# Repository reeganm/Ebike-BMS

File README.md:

# Ebike-BMS
Battery Management system for an Ebike

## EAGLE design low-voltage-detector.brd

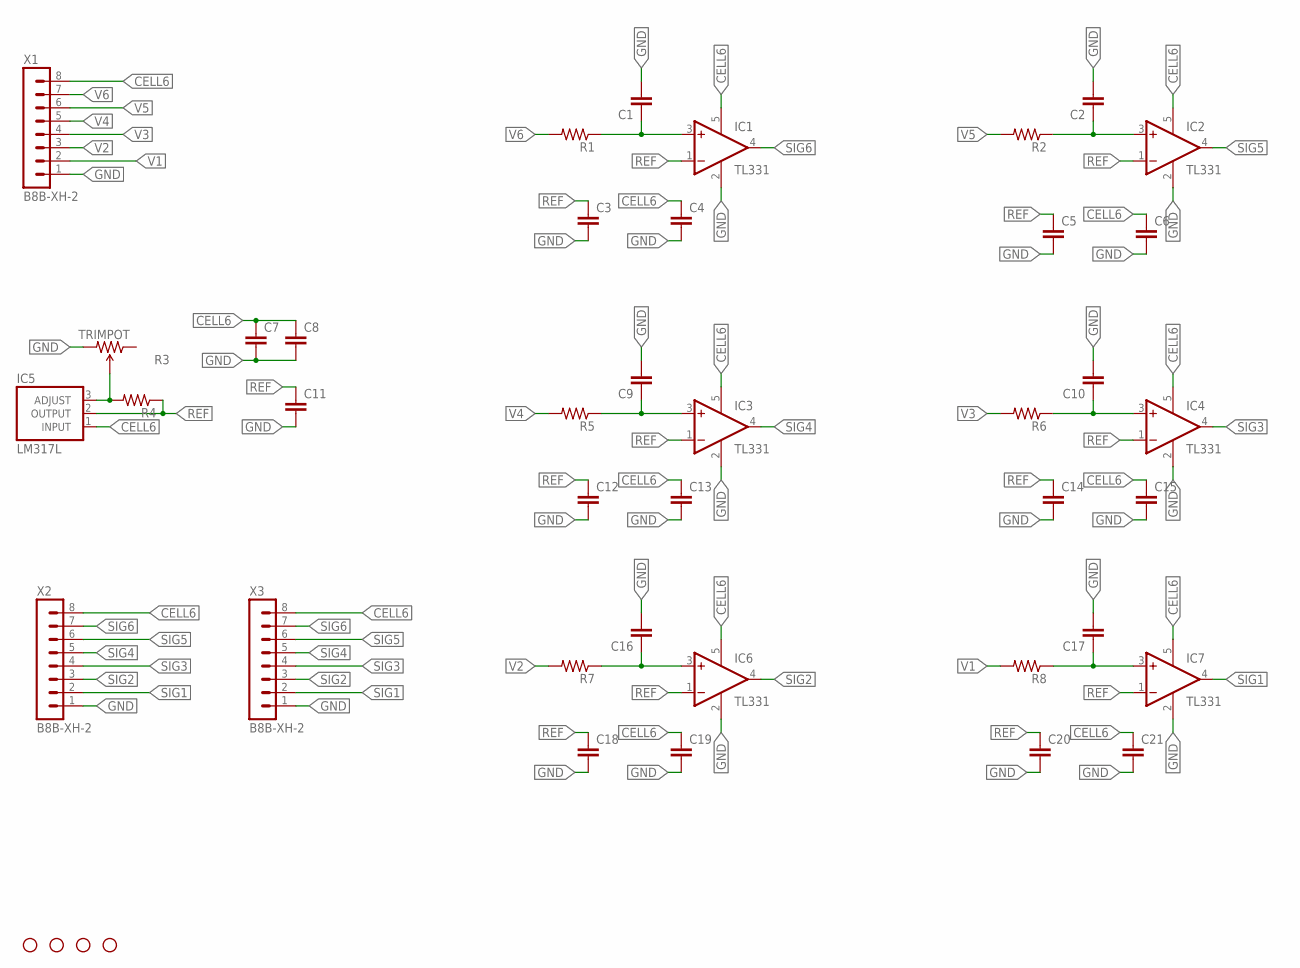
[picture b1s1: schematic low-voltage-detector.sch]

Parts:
C1, C2, C3, C4, C5, C6, C7, C8, C9, C10, C11, C12, C13, C14, C15, C16, C17, C18, C19, C20, C21: CAPACITOR_0805; 0805
H1, H2, H3, H4: STAND-OFF
IC1, IC2, IC3, IC4, IC6, IC7: TL331; DBV-R-PDSO-G5
IC5: LM317L; TO92
R1, R2, R4, R5, R6, R7, R8: R-US_R0805; R0805
R3: TRIMPOT; 490-2877-ND
X1, X2, X3: B8B-XH-2; B8B-XH-A

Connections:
CELL6: C4.1, C6.1, C7.1, C8.1, C13.1, C15.1, C19.1, C21.1, IC1.5 (V+), IC2.5 (V+), IC3.5 (V+), IC4.5 (V+), IC5.1 (INPUT), IC6.5 (V+), IC7.5 (V+), X1.8, X2.8, X3.8
GND: C1.2, C2.2, C3.2, C4.2, C5.2, C6.2, C7.2, C8.2, C9.2, C10.2, C11.2, C12.2, C13.2, C14.2, C15.2, C16.2, C17.2, C18.2, C19.2, C20.2, C21.2, IC1.2 (GND), IC2.2 (GND), IC3.2 (GND), IC4.2 (GND), IC6.2 (GND), IC7.2 (GND), R3.P$3 (CW), X1.1, X2.1, X3.1
unnamed: C1.1, IC1.3 (+IN), R1.1
unnamed: C2.1, IC2.3 (+IN), R2.1
unnamed: C9.1, IC3.3 (+IN), R5.1
unnamed: C10.1, IC4.3 (+IN), R6.1
unnamed: C16.1, IC6.3 (+IN), R7.1
unnamed: C17.1, IC7.3 (+IN), R8.1
unnamed: IC5.3 (ADJUST), R3.P$2 (WIPER), R4.2
REF: C3.1, C5.1, C11.1, C12.1, C14.1, C18.1, C20.1, IC1.1 (-IN), IC2.1 (-IN), IC3.1 (-IN), IC4.1 (-IN), IC5.2 (OUTPUT), IC6.1 (-IN), IC7.1 (-IN), R4.1
SIG1: IC7.4 (OUT), X2.2, X3.2
SIG2: IC6.4 (OUT), X2.3, X3.3
SIG3: IC4.4 (OUT), X2.4, X3.4
SIG4: IC3.4 (OUT), X2.5, X3.5
SIG5: IC2.4 (OUT), X2.6, X3.6
SIG6: IC1.4 (OUT), X2.7, X3.7
V1: R8.2, X1.2
V2: R7.2, X1.3
V3: R6.2, X1.4
V4: R5.2, X1.5
V5: R2.2, X1.6
V6: R1.2, X1.7

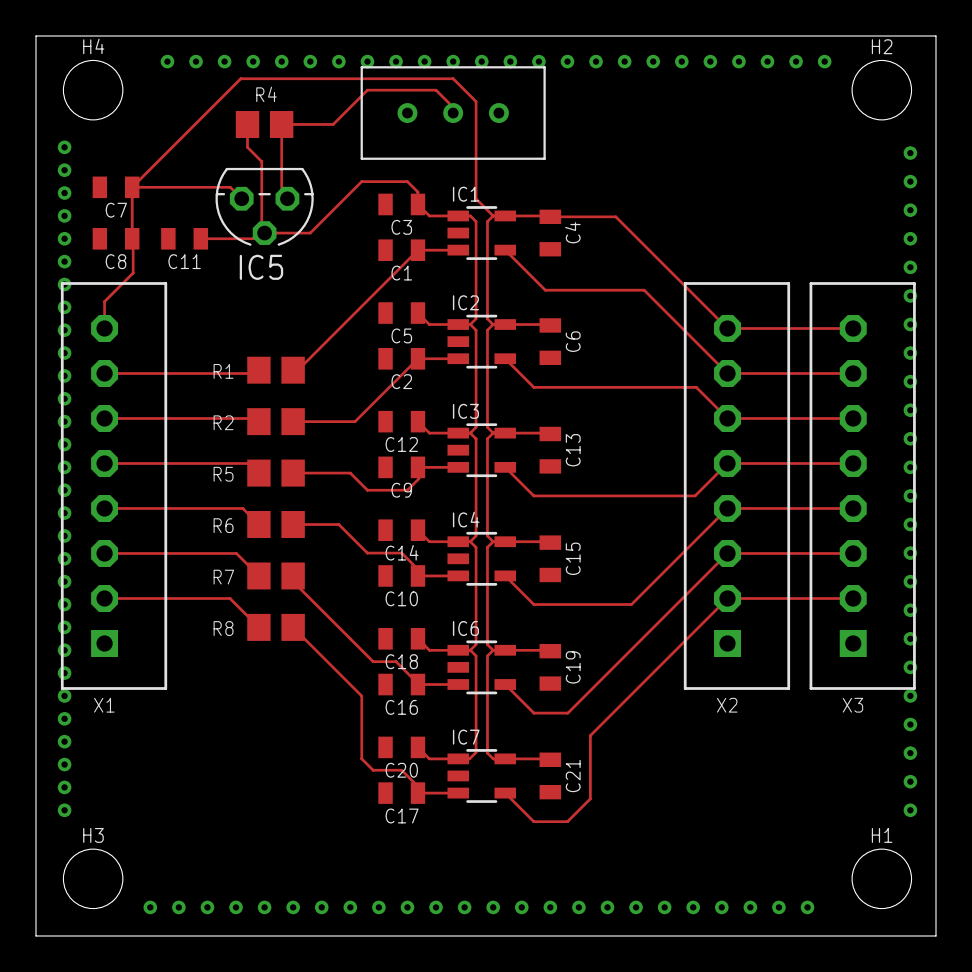
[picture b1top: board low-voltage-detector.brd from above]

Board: 2 copper layers, 50.0 x 50.0 mm, 43 parts (0 on the bottom side), 22 nets.

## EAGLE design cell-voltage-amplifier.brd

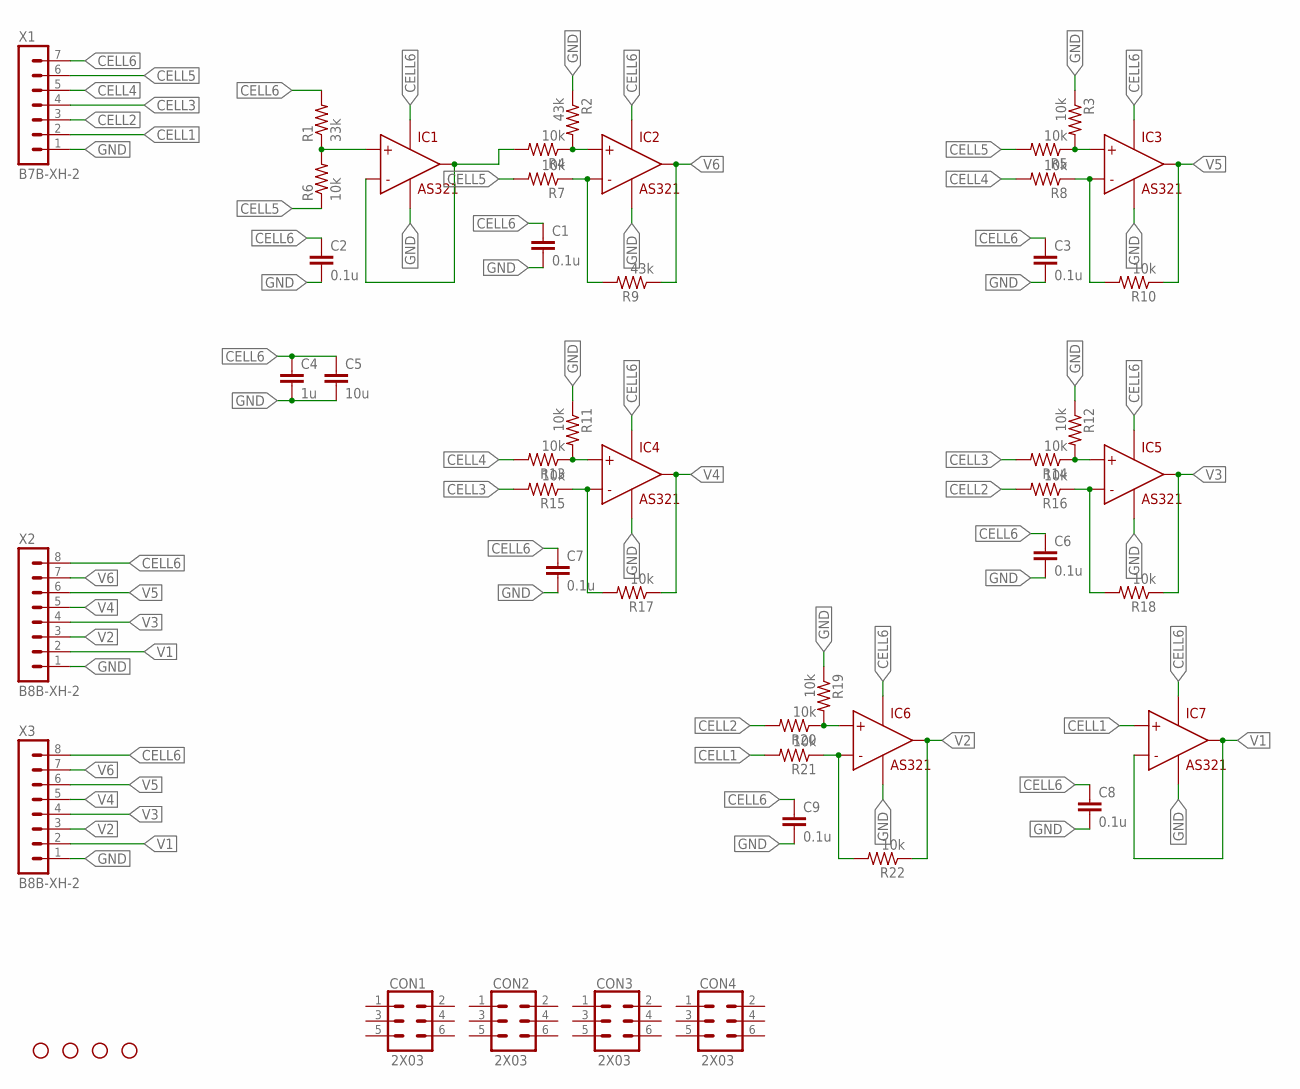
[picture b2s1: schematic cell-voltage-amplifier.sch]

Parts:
C1, C2, C3, C6, C7, C8, C9: 0.1u; 0805
C4: 1u; 0805
C5: 10u; 0805
CON1, CON2, CON3, CON4: 2X03
H1, H2, H3, H4: STAND-OFF
IC1, IC2, IC3, IC4, IC5, IC6, IC7: AS321
R1: 33k; R0805
R2, R9: 43k; R0805
R3, R4, R5, R6, R7, R8, R10, R11, R12, R13, R14, R15, R16, R17, R18, R19, R20, R21, R22: 10k; R0805
X1: B7B-XH-2; B7B-XH-A
X2, X3: B8B-XH-2; B8B-XH-A

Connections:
CELL1: IC7.1 (I+), R21.2, X1.2
CELL2: R16.2, R20.2, X1.3
CELL3: R14.2, R15.2, X1.4
CELL4: R8.2, R13.2, X1.5
CELL5: R5.2, R6.1, R7.2, X1.6
CELL6: C1.1, C2.1, C3.1, C4.1, C5.1, C6.1, C7.1, C8.1, C9.1, IC1.5 (V+), IC2.5 (V+), IC3.5 (V+), IC4.5 (V+), IC5.5 (V+), IC6.5 (V+), IC7.5 (V+), R1.2, X1.7, X2.8, X3.8
GND: C1.2, C2.2, C3.2, C4.2, C5.2, C6.2, C7.2, C8.2, C9.2, IC1.2 (V-), IC2.2 (V-), IC3.2 (V-), IC4.2 (V-), IC5.2 (V-), IC6.2 (V-), IC7.2 (V-), R2.1, R3.1, R11.1, R12.1, R19.1, X1.1, X2.1, X3.1
unnamed: IC1.3 (I-), IC1.4 (OUT), R4.2
unnamed: IC1.1 (I+), R1.1, R6.2
unnamed: IC2.1 (I+), R2.2, R4.1
unnamed: IC2.3 (I-), R7.1, R9.2
unnamed: IC4.1 (I+), R11.2, R13.1
unnamed: IC4.3 (I-), R15.1, R17.2
unnamed: IC3.1 (I+), R3.2, R5.1
unnamed: IC3.3 (I-), R8.1, R10.2
unnamed: IC5.1 (I+), R12.2, R14.1
unnamed: IC5.3 (I-), R16.1, R18.2
unnamed: IC6.1 (I+), R19.2, R20.1
unnamed: IC6.3 (I-), R21.1, R22.2
V1: IC7.3 (I-), IC7.4 (OUT), X2.2, X3.2
V2: IC6.4 (OUT), R22.1, X2.3, X3.3
V3: IC5.4 (OUT), R18.1, X2.4, X3.4
V4: IC4.4 (OUT), R17.1, X2.5, X3.5
V5: IC3.4 (OUT), R10.1, X2.6, X3.6
V6: IC2.4 (OUT), R9.1, X2.7, X3.7

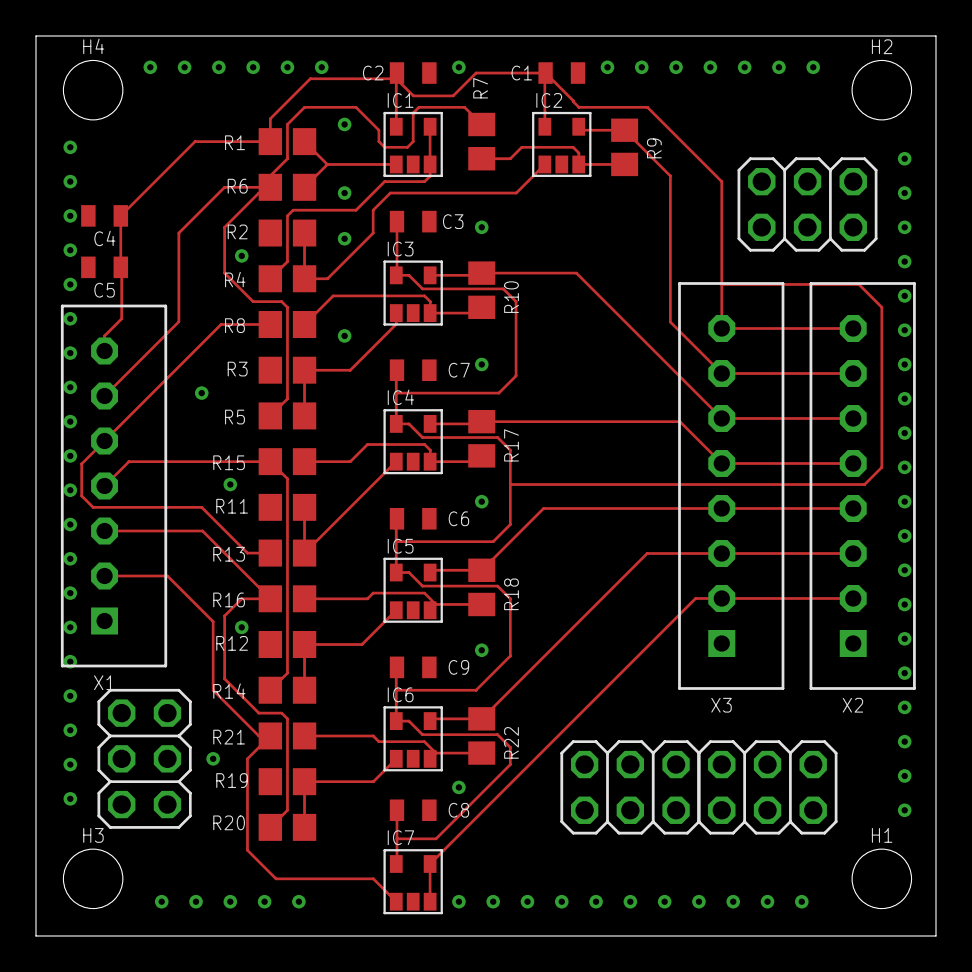
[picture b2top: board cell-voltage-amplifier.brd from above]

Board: 2 copper layers, 50.0 x 50.0 mm, 49 parts (0 on the bottom side), 25 nets.

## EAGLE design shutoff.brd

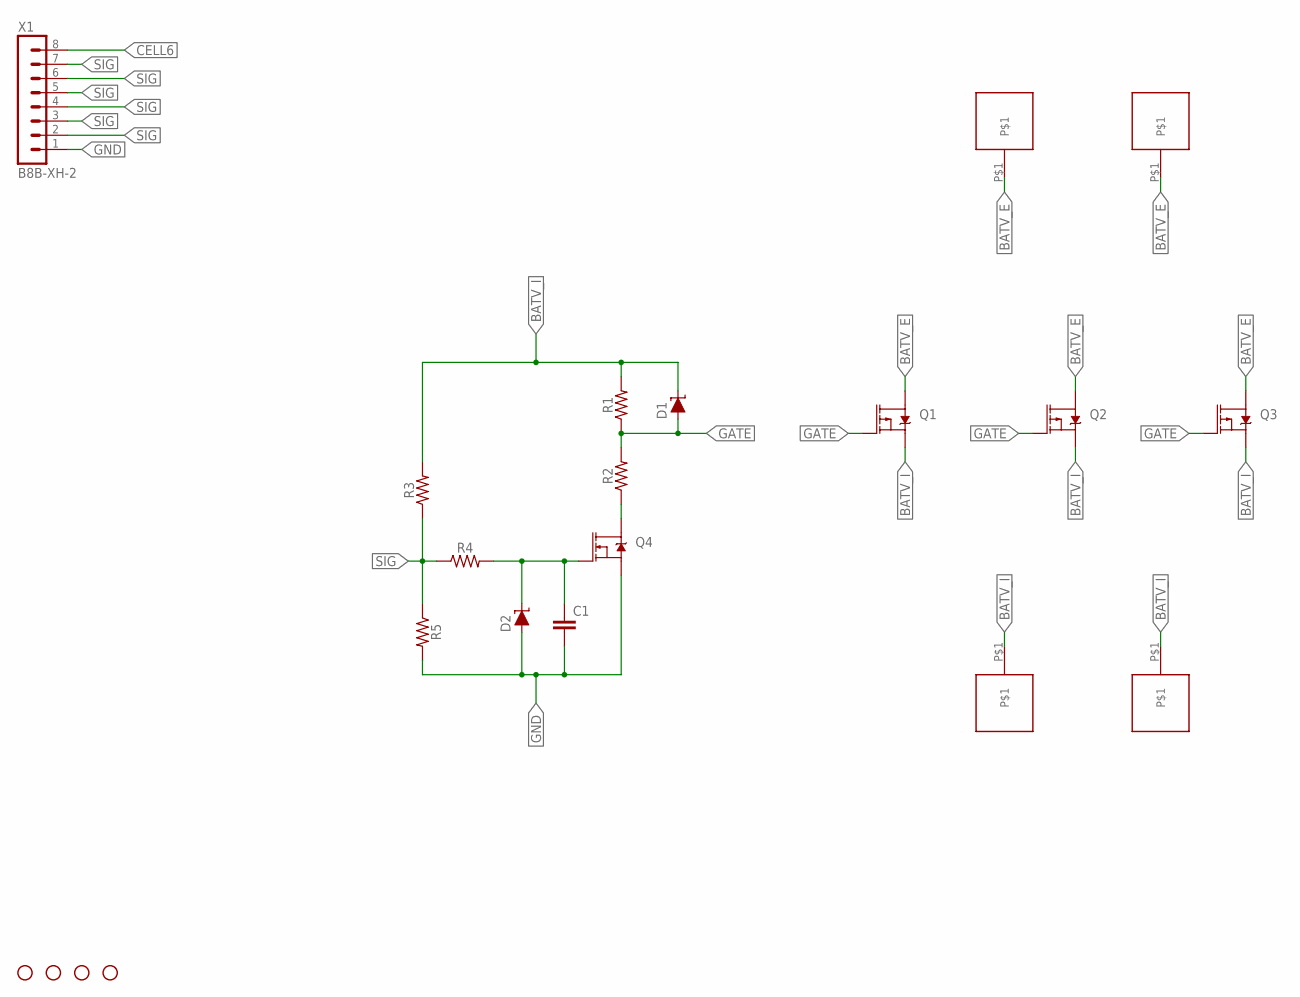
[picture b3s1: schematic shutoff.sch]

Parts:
C1: CAPACITOR_0805; 0805
D1, D2: DIODE_TVS_DO-214AA; DO214AA
H1, H2, H3, H4: STAND-OFF
Q1, Q2, Q3: MOSFET_PMOS_TO-263; TO-263/D2PAK
Q4: MOSFET_NMOS_TO-263; TO-263/D2PAK
R1, R2, R3, R4, R5: RESISTOR_0805; 0805
W1, W2, W3, W4: 16G
X1: B8B-XH-2; B8B-XH-A

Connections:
BATV_E: Q1.2 (D), Q2.2 (D), Q3.2 (D), W1.P$1, W2.P$1
BATV_I: D1.C, Q1.3 (S), Q2.3 (S), Q3.3 (S), R1.2, R3.2, W3.P$1, W4.P$1
CELL6: X1.8
GATE: D1.A, Q1.1 (G), Q2.1 (G), Q3.1 (G), R1.1, R2.2
GND: C1.2, D2.A, Q4.3 (S), R5.2, X1.1
unnamed: Q4.2 (D), R2.1
unnamed: C1.1, D2.C, Q4.1 (G), R4.2
SIG: R3.1, R4.1, R5.1, X1.2, X1.3, X1.4, X1.5, X1.6, X1.7

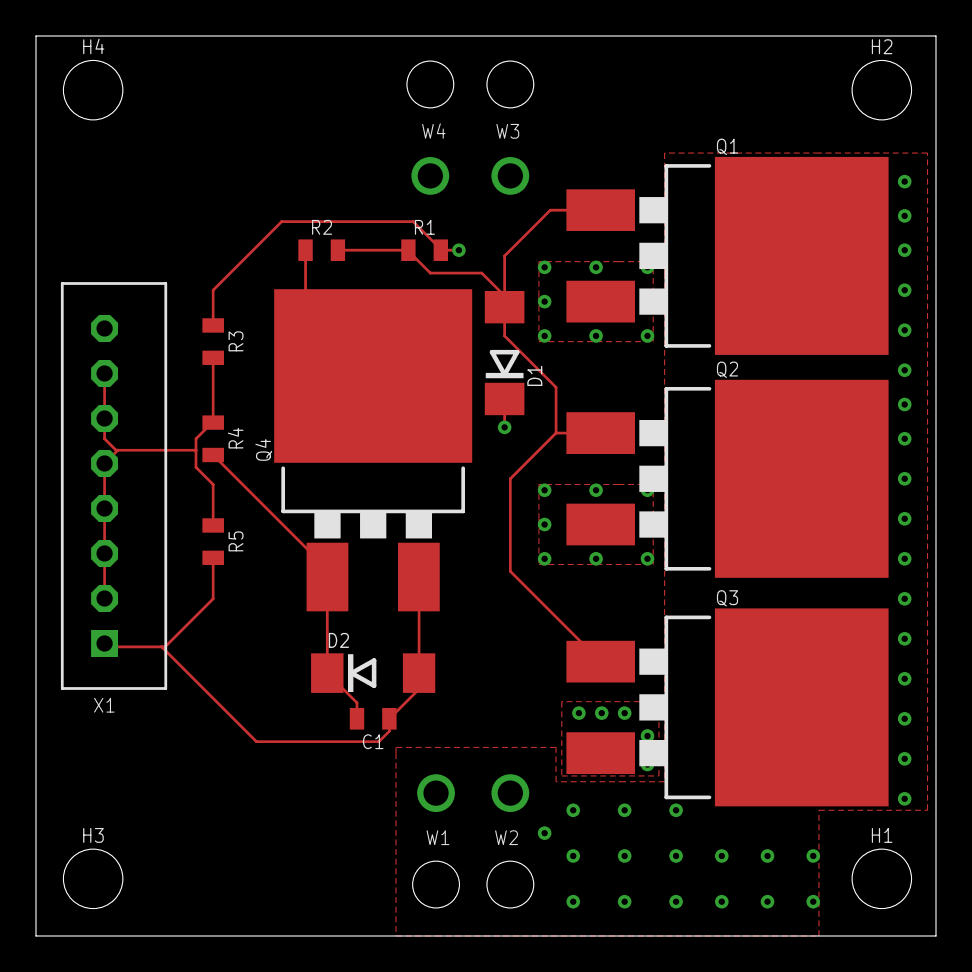
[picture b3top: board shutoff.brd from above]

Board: 2 copper layers, 50.0 x 50.0 mm, 21 parts (0 on the bottom side), 7 nets.

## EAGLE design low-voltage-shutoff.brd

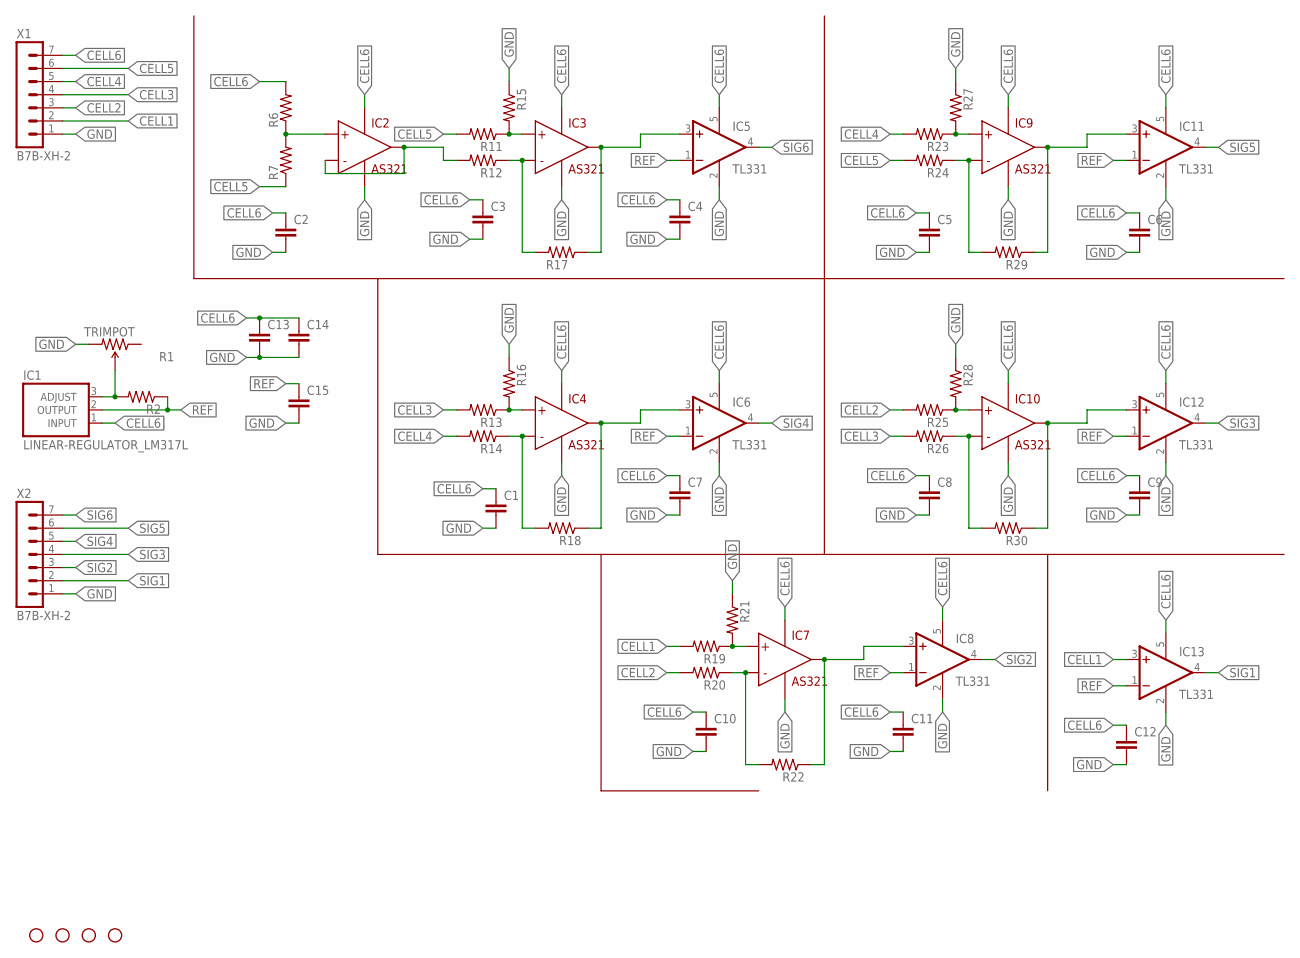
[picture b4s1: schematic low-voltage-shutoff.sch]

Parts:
C1, C2, C3, C4, C5, C6, C7, C8, C9, C10, C11, C12, C13, C14, C15: CAPACITOR_0805; 0805
H1, H2, H3, H4: STAND-OFF
IC1: LINEAR-REGULATOR_LM317L; TO92
IC2, IC3, IC4, IC7, IC9, IC10: AS321
IC5, IC6, IC8, IC11, IC12, IC13: TL331; DBV-R-PDSO-G5
R1: TRIMPOT; 490-2877-ND
R2, R6, R7, R11, R12, R13, R14, R15, R16, R17, R18, R19, R20, R21, R22, R23, R24, R25, R26, R27, R28, R29, R30: R-US_R0805; R0805
X1, X2: B7B-XH-2; B7B-XH-A

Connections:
CELL1: IC13.3 (+IN), R19.2, X1.2
CELL2: R20.2, R25.2, X1.3
CELL3: R13.2, R26.2, X1.4
CELL4: R14.2, R23.2, X1.5
CELL5: R7.1, R11.2, R24.2, X1.6
CELL6: C1.1, C2.1, C3.1, C4.1, C5.1, C6.1, C7.1, C8.1, C9.1, C10.1, C11.1, C12.1, C13.1, C14.1, IC1.1 (INPUT), IC2.5 (V+), IC3.5 (V+), IC4.5 (V+), IC5.5 (V+), IC6.5 (V+), IC7.5 (V+), IC8.5 (V+), IC9.5 (V+), IC10.5 (V+), IC11.5 (V+), IC12.5 (V+), IC13.5 (V+), R6.2, X1.7
GND: C1.2, C2.2, C3.2, C4.2, C5.2, C6.2, C7.2, C8.2, C9.2, C10.2, C11.2, C12.2, C13.2, C14.2, C15.2, IC2.2 (V-), IC3.2 (V-), IC4.2 (V-), IC5.2 (GND), IC6.2 (GND), IC7.2 (V-), IC8.2 (GND), IC9.2 (V-), IC10.2 (V-), IC11.2 (GND), IC12.2 (GND), IC13.2 (GND), R1.P$3 (CW), R15.1, R16.1, R21.1, R27.1, R28.1, X1.1, X2.1
unnamed: IC2.3 (I-), IC2.4 (OUT), R12.2
unnamed: IC2.1 (I+), R6.1, R7.2
unnamed: IC3.1 (I+), R11.1, R15.2
unnamed: IC3.3 (I-), R12.1, R17.2
unnamed: IC3.4 (OUT), IC5.3 (+IN), R17.1
unnamed: IC4.1 (I+), R13.1, R16.2
unnamed: IC4.3 (I-), R14.1, R18.2
unnamed: IC9.1 (I+), R23.1, R27.2
unnamed: IC9.3 (I-), R24.1, R29.2
unnamed: IC9.4 (OUT), IC11.3 (+IN), R29.1
unnamed: IC4.4 (OUT), IC6.3 (+IN), R18.1
unnamed: IC10.1 (I+), R25.1, R28.2
unnamed: IC10.3 (I-), R26.1, R30.2
unnamed: IC10.4 (OUT), IC12.3 (+IN), R30.1
unnamed: IC7.1 (I+), R19.1, R21.2
unnamed: IC7.3 (I-), R20.1, R22.2
unnamed: IC7.4 (OUT), IC8.3 (+IN), R22.1
unnamed: IC1.3 (ADJUST), R1.P$2 (WIPER), R2.2
REF: C15.1, IC1.2 (OUTPUT), IC5.1 (-IN), IC6.1 (-IN), IC8.1 (-IN), IC11.1 (-IN), IC12.1 (-IN), IC13.1 (-IN), R2.1
SIG1: IC13.4 (OUT), X2.2
SIG2: IC8.4 (OUT), X2.3
SIG3: IC12.4 (OUT), X2.4
SIG4: IC6.4 (OUT), X2.5
SIG5: IC11.4 (OUT), X2.6
SIG6: IC5.4 (OUT), X2.7

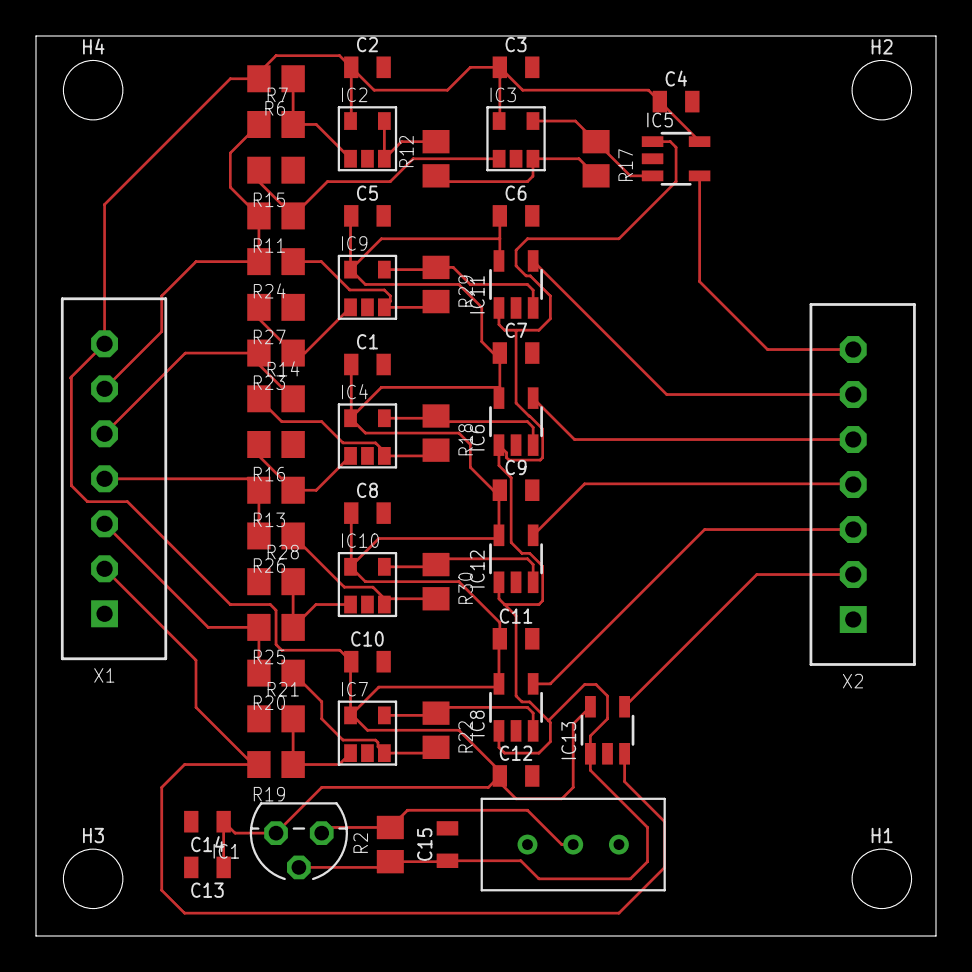
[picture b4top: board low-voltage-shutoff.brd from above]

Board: 2 copper layers, 50.0 x 50.0 mm, 58 parts (0 on the bottom side), 32 nets.

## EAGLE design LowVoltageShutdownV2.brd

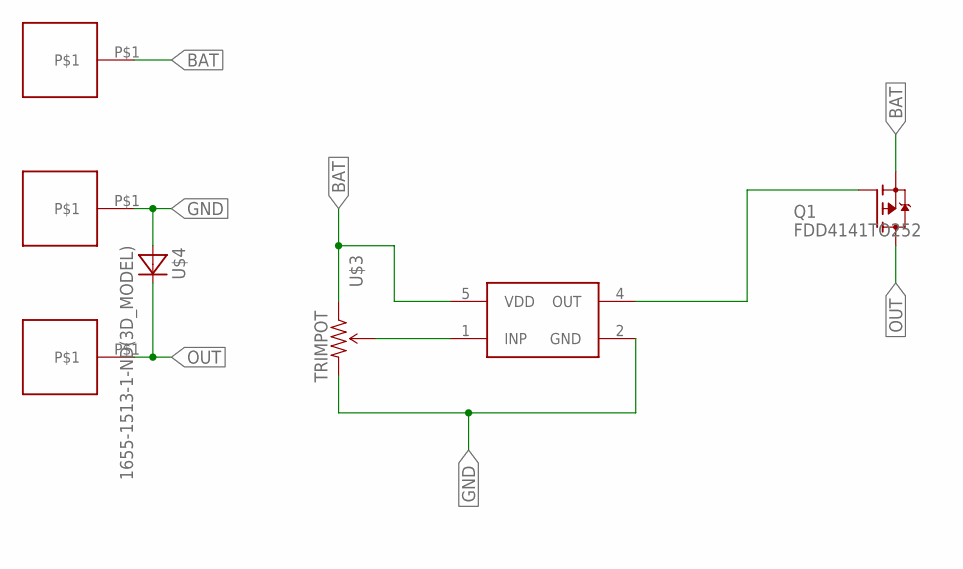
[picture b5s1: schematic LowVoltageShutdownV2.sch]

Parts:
OUT: 16G
Q1: FDD4141TO252; TO252
U$1: MIC842L(3D_MODEL); SOTFL65P210X110-5
U$3: TRIMPOT; 490-2877-ND
U$4: 1655-1513-1-ND(3D_MODEL); DIOAD1950W130L900D530B
U$5, U$6: 450PAD

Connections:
BAT: Q1.2 (S), U$1.5 (VDD), U$3.P$1 (CCW), U$5.P$1
GND: U$1.2 (GND), U$3.P$3 (CW), U$4.2 (A), U$6.P$1
unnamed: U$1.1 (INP), U$3.P$2 (WIPER)
unnamed: Q1.1 (G), U$1.4 (OUT)
OUT: OUT.P$1, Q1.3 (D), U$4.1 (C)

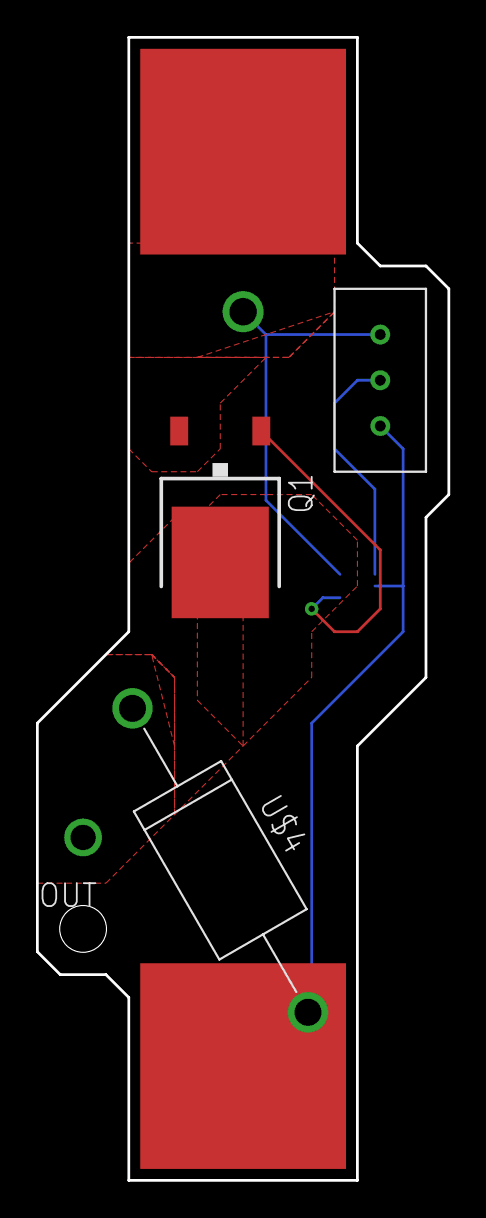
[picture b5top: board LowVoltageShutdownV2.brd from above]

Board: 2 copper layers, 22.9 x 63.5 mm, 7 parts (1 on the bottom side), 5 nets.

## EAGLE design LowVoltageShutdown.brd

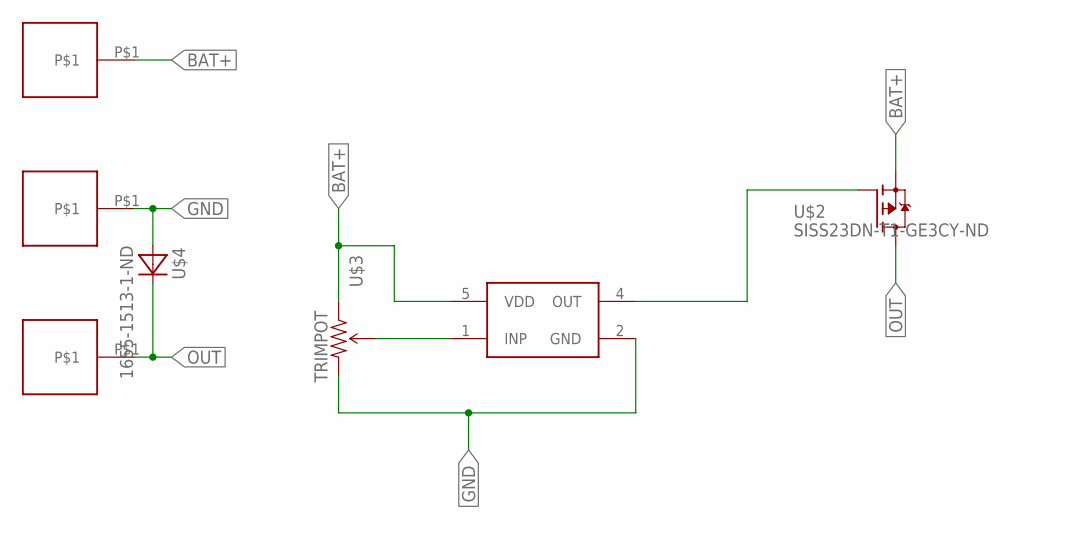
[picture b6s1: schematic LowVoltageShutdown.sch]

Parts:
BAT+: 16G
GND: 16G
OUT: 16G
U$1: MIC842L; SC70
U$2: SISS23DN-T1-GE3CY-ND; POWERPAK1212-8S
U$3: TRIMPOT; 490-2877-ND
U$4: 1655-1513-1-ND

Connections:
BAT+: BAT+.P$1, U$1.5 (VDD), U$2.S, U$3.P$1 (CCW)
GND: GND.P$1, U$1.2 (GND), U$3.P$3 (CW), U$4.A
unnamed: U$1.1 (INP), U$3.P$2 (WIPER)
unnamed: U$1.4 (OUT), U$2.G
OUT: OUT.P$1, U$2.D, U$4.C

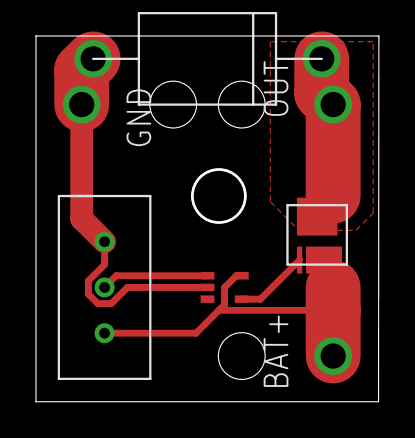
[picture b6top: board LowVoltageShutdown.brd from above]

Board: 2 copper layers, 18.9 x 20.2 mm, 7 parts (0 on the bottom side), 5 nets.

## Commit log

2018-04-25 first revision of low voltage shutoff complete
2018-05-19 second revision and added 3D models
2018-05-23 added ground pin
2020-04-24 Saving partial work
2020-04-24 saving
2020-04-25 Done Routing
2020-04-29 Fix schematic
2020-04-29 Fix routing
2020-04-29 More updates and gerbers
